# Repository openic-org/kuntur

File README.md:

# Kuntur

**Kuntur** (Quechua for *condor*) is an open neural-recording headstage
built around Intan RHD2164 amplifiers, a Lattice CrossLink-NX FPGA and an
STM32WB09 Bluetooth LE microcontroller, together with the firmware, FPGA
designs and desktop software that go with it.

> **Status: pre-release, research use only.** This repository is under
> active development ahead of a first public release. Interfaces, file
> formats and hardware revisions may still change. Not for clinical use.

Kuntur has two data paths:

- **Wireless:** the headstage streams over BLE (2M PHY) to a NUCLEO-WB09KE
  running the **BLE–USB bridge** firmware, which forwards packets over USB
  serial to **Tunki** (Quechua for the Andean cock-of-the-rock, Peru's
  national bird), the desktop app for live display and recording.
- **Wired:** the headstage sends its samples over an LVDS link to the
  **RHD adapter**, a CrossLink-NX FPGA design that appears to an RHD-protocol
  recording controller as two RHD2164 chips.

## Repository layout

```
hardware/      KiCad designs, fab packages, BOMs and pick-and-place files
  kuntur144-ecl/            headstage digital board: FPGA, BLE MCU, power
  kuntur144-nil/            headstage front-end board: recording and stimulation sheets
  kuntur144-omnetics/       Omnetics connector board
  kuntur144-prog/           programming board
  kuntur144-prog-adapter/   programming adapter
fpga/          Lattice Radiant projects
  headstage/                headstage FPGA (LIFCL-17)
  rhd-adapter/              RHD adapter (LIFCL-40)
  scripts/                  build and testbench helpers
firmware/
  headstage/                STM32WB09 headstage firmware (STM32CubeIDE project)
  ble-usb-bridge/           NUCLEO-WB09KE BLE central → USB serial bridge (Makefile)
software/
  tunki/                    PyQt6 desktop app: live display, recording, analysis
tools/                      analysis and validation tools (for now in software/tunki/)
```

## Building

**Tunki** (Python ≥ 3.11):

```bash
cd software/tunki
pip install -r requirements.txt
python main.py
```

**Firmware** needs the Arm GNU toolchain shipped with STM32CubeIDE and the
STM32Cube WB0 firmware packages (V1.4.0, and V1.4.1 for the bridge), found by
default under `~/STM32Cube/Repository`, where STM32CubeIDE installs them. For
another location, set `STM32CUBE_REPO` (bridge) or `STM32CUBE_FW_WB0` (headstage,
see `firmware/headstage/makefile.init`) on the `make` command line.

```bash
cd firmware/headstage/Debug && make all -j8     # → kuntur-mcu.elf / .hex
cd firmware/ble-usb-bridge && make -j8          # → build/ble_usb_bridge.bin
```

**FPGA** projects open in Lattice Radiant 2025.2 (`fpga/headstage/kuntur_fpga.rdf`,
`fpga/rhd-adapter/intan_rec_adapter.rdf`). Released bitstreams are tracked
next to each implementation (`impl_*/*.bit`).

## Licences

- `hardware/` and `fpga/`: **CERN Open Hardware Licence v2 – Permissive**
  (`LICENSES/CERN-OHL-P-2.0.txt`)
- everything else: **Apache License 2.0** (`LICENSES/Apache-2.0.txt`)

Third-party files (ST and Lattice generated code, the vendored bridge base in
`firmware/ble-usb-bridge/base/`) keep their own notices. See `LICENSE`.

Intan, RHD2164 and RHX are trademarks of Intan Technologies; this project is
not affiliated with or endorsed by Intan Technologies.

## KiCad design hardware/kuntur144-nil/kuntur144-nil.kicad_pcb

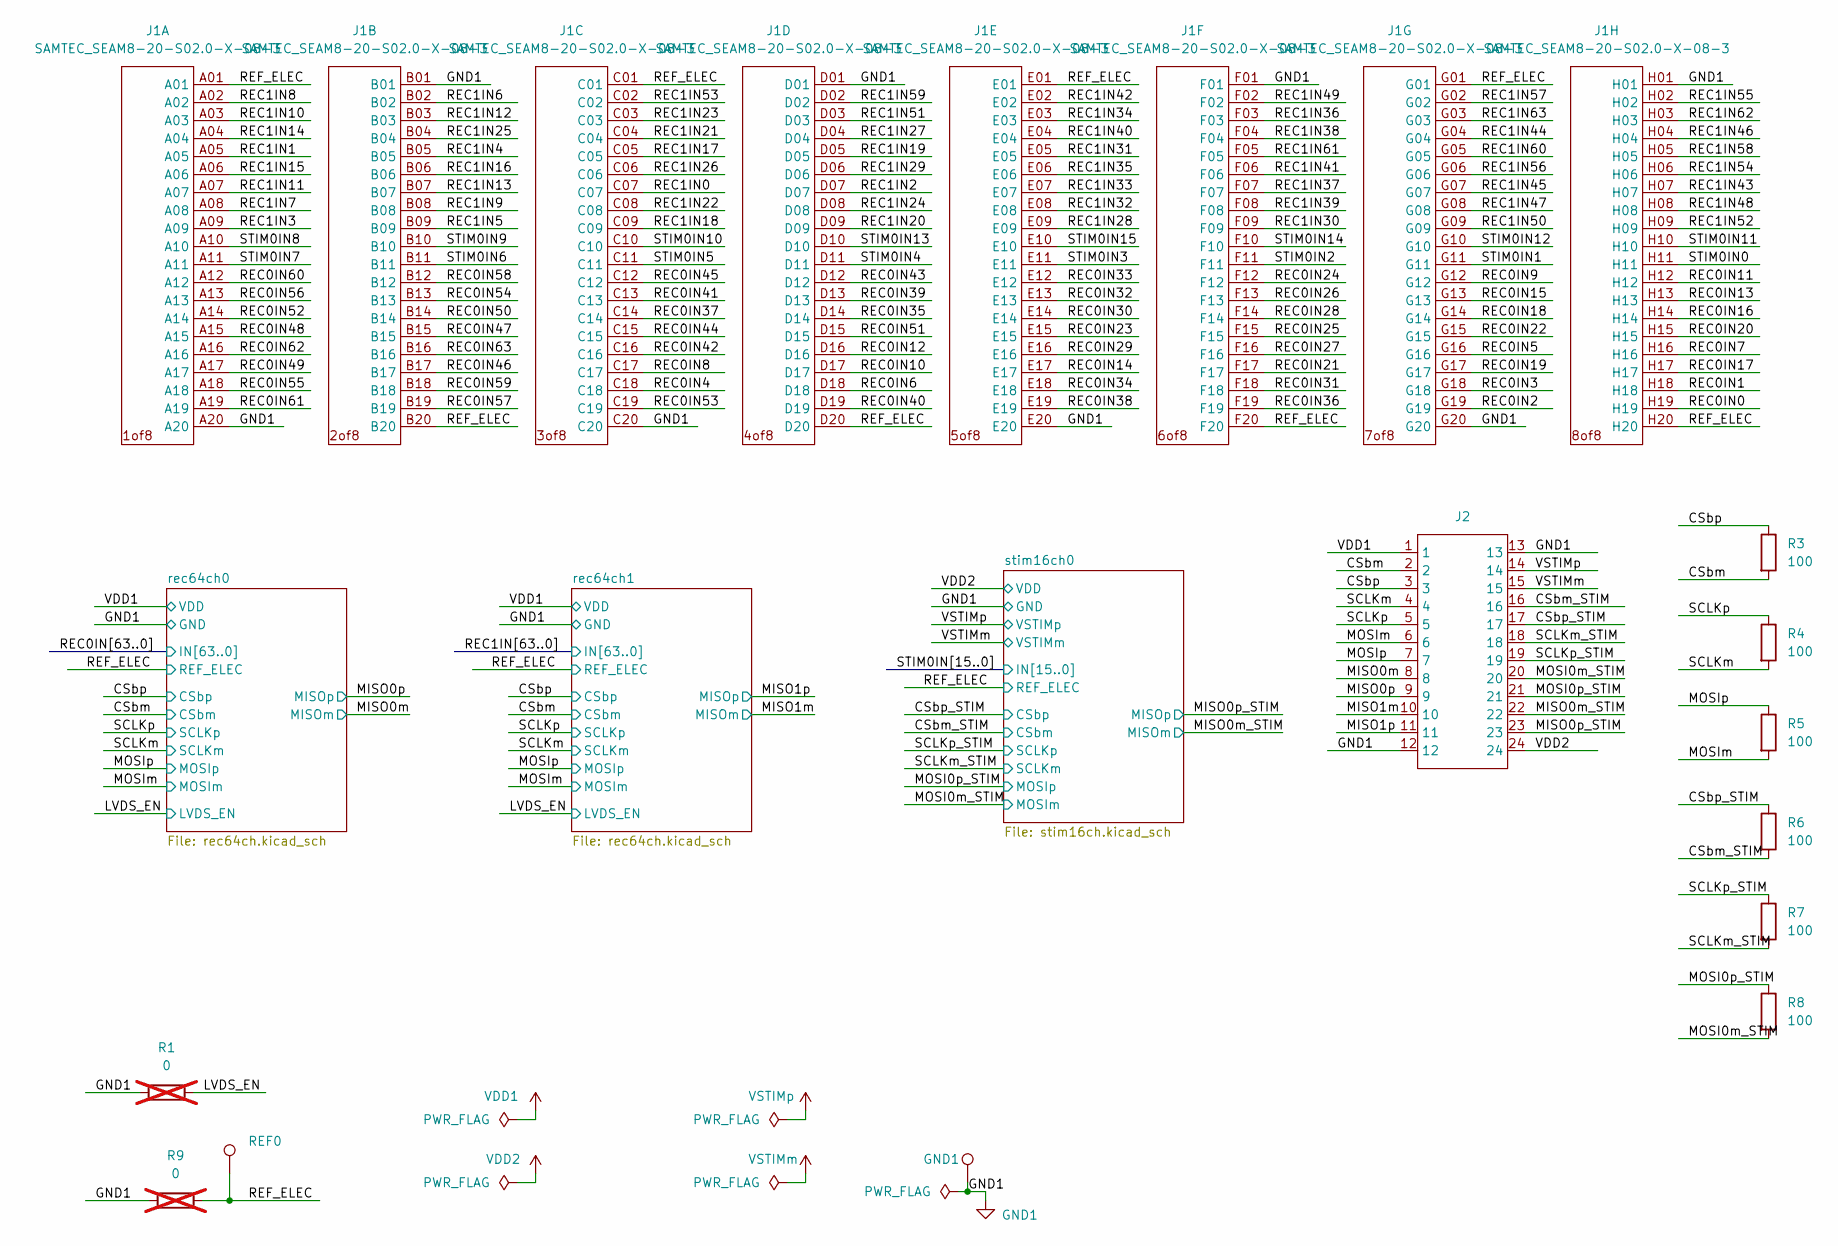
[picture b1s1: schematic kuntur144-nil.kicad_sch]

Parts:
GND1: GND1; TESTPOINT_SMALL
J1: SAMTEC_SEAM8-20-S02.0-X-08-3; MPN SEAM8-20-S02.0-S-08-3
J2: DF40C(2.0)-24DS-0.4V; MPN DF40C(2.0)-24DS-0.4V
R1, R9: 0; R_0201_0603Metric; MPN RC0201FR-070RL; not fitted
R3, R4, R5, R6, R7, R8: 100; R_0201_0603Metric; MPN RC0201FR-07100RL
REF0: REF0; TESTPOINT_SMALL

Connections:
/CSbm: J2.2, R3.2; also elsewhere on the board
/CSbm_STIM: J2.16, R6.2; also elsewhere on the board
/CSbp: J2.3, R3.1; also elsewhere on the board
/CSbp_STIM: J2.17, R6.1; also elsewhere on the board
/LVDS_EN: R1.2; also elsewhere on the board
/MISO0m: J2.8; also elsewhere on the board
/MISO0m_STIM: J2.22; also elsewhere on the board
/MISO0p: J2.9; also elsewhere on the board
/MISO0p_STIM: J2.23; also elsewhere on the board
/MISO1m: J2.10; also elsewhere on the board
/MISO1p: J2.11; also elsewhere on the board
/MOSI0m_STIM: J2.20, R8.2; also elsewhere on the board
/MOSI0p_STIM: J2.21, R8.1; also elsewhere on the board
/MOSIm: J2.6, R5.2; also elsewhere on the board
/MOSIp: J2.7, R5.1; also elsewhere on the board
/REC0IN0: J1.H19; also elsewhere on the board
/REC0IN1: J1.H18; also elsewhere on the board
/REC0IN2: J1.G19; also elsewhere on the board
/REC0IN3: J1.G18; also elsewhere on the board
/REC0IN4: J1.C18; also elsewhere on the board
/REC0IN5: J1.G16; also elsewhere on the board
/REC0IN6: J1.D18; also elsewhere on the board
/REC0IN7: J1.H16; also elsewhere on the board
/REC0IN8: J1.C17; also elsewhere on the board
/REC0IN9: J1.G12; also elsewhere on the board
/REC0IN10: J1.D17; also elsewhere on the board
/REC0IN11: J1.H12; also elsewhere on the board
/REC0IN12: J1.D16; also elsewhere on the board
/REC0IN13: J1.H13; also elsewhere on the board
/REC0IN14: J1.E17; also elsewhere on the board
/REC0IN15: J1.G13; also elsewhere on the board
/REC0IN16: J1.H14; also elsewhere on the board
/REC0IN17: J1.H17; also elsewhere on the board
/REC0IN18: J1.G14; also elsewhere on the board
/REC0IN19: J1.G17; also elsewhere on the board
/REC0IN20: J1.H15; also elsewhere on the board
/REC0IN21: J1.F17; also elsewhere on the board
/REC0IN22: J1.G15; also elsewhere on the board
/REC0IN23: J1.E15; also elsewhere on the board
/REC0IN24: J1.F12; also elsewhere on the board
/REC0IN25: J1.F15; also elsewhere on the board
/REC0IN26: J1.F13; also elsewhere on the board
/REC0IN27: J1.F16; also elsewhere on the board
/REC0IN28: J1.F14; also elsewhere on the board
/REC0IN29: J1.E16; also elsewhere on the board
/REC0IN30: J1.E14; also elsewhere on the board
/REC0IN31: J1.F18; also elsewhere on the board
/REC0IN32: J1.E13; also elsewhere on the board
/REC0IN33: J1.E12; also elsewhere on the board
/REC0IN34: J1.E18; also elsewhere on the board
/REC0IN35: J1.D14; also elsewhere on the board
/REC0IN36: J1.F19; also elsewhere on the board
/REC0IN37: J1.C14; also elsewhere on the board
/REC0IN38: J1.E19; also elsewhere on the board
/REC0IN39: J1.D13; also elsewhere on the board
/REC0IN40: J1.D19; also elsewhere on the board
/REC0IN41: J1.C13; also elsewhere on the board
/REC0IN42: J1.C16; also elsewhere on the board
/REC0IN43: J1.D12; also elsewhere on the board
/REC0IN44: J1.C15; also elsewhere on the board
/REC0IN45: J1.C12; also elsewhere on the board
/REC0IN46: J1.B17; also elsewhere on the board
/REC0IN47: J1.B15; also elsewhere on the board
/REC0IN48: J1.A15; also elsewhere on the board
/REC0IN49: J1.A17; also elsewhere on the board
/REC0IN50: J1.B14; also elsewhere on the board
/REC0IN51: J1.D15; also elsewhere on the board
/REC0IN52: J1.A14; also elsewhere on the board
/REC0IN53: J1.C19; also elsewhere on the board
/REC0IN54: J1.B13; also elsewhere on the board
/REC0IN55: J1.A18; also elsewhere on the board
/REC0IN56: J1.A13; also elsewhere on the board
/REC0IN57: J1.B19; also elsewhere on the board
/REC0IN58: J1.B12; also elsewhere on the board
/REC0IN59: J1.B18; also elsewhere on the board
/REC0IN60: J1.A12; also elsewhere on the board
/REC0IN61: J1.A19; also elsewhere on the board
/REC0IN62: J1.A16; also elsewhere on the board
/REC0IN63: J1.B16; also elsewhere on the board
/REC1IN0: J1.C07; also elsewhere on the board
/REC1IN1: J1.A05; also elsewhere on the board
/REC1IN2: J1.D07; also elsewhere on the board
/REC1IN3: J1.A09; also elsewhere on the board
/REC1IN4: J1.B05; also elsewhere on the board
/REC1IN5: J1.B09; also elsewhere on the board
/REC1IN6: J1.B02; also elsewhere on the board
/REC1IN7: J1.A08; also elsewhere on the board
/REC1IN8: J1.A02; also elsewhere on the board
/REC1IN9: J1.B08; also elsewhere on the board
/REC1IN10: J1.A03; also elsewhere on the board
/REC1IN11: J1.A07; also elsewhere on the board
/REC1IN12: J1.B03; also elsewhere on the board
/REC1IN13: J1.B07; also elsewhere on the board
/REC1IN14: J1.A04; also elsewhere on the board
/REC1IN15: J1.A06; also elsewhere on the board
/REC1IN16: J1.B06; also elsewhere on the board
/REC1IN17: J1.C05; also elsewhere on the board
/REC1IN18: J1.C09; also elsewhere on the board
/REC1IN19: J1.D05; also elsewhere on the board
/REC1IN20: J1.D09; also elsewhere on the board
/REC1IN21: J1.C04; also elsewhere on the board
/REC1IN22: J1.C08; also elsewhere on the board
/REC1IN23: J1.C03; also elsewhere on the board
/REC1IN24: J1.D08; also elsewhere on the board
/REC1IN25: J1.B04; also elsewhere on the board
/REC1IN26: J1.C06; also elsewhere on the board
/REC1IN27: J1.D04; also elsewhere on the board
/REC1IN28: J1.E09; also elsewhere on the board
/REC1IN29: J1.D06; also elsewhere on the board
/REC1IN30: J1.F09; also elsewhere on the board
/REC1IN31: J1.E05; also elsewhere on the board
/REC1IN32: J1.E08; also elsewhere on the board
/REC1IN33: J1.E07; also elsewhere on the board
/REC1IN34: J1.E03; also elsewhere on the board
/REC1IN35: J1.E06; also elsewhere on the board
/REC1IN36: J1.F03; also elsewhere on the board
/REC1IN37: J1.F07; also elsewhere on the board
/REC1IN38: J1.F04; also elsewhere on the board
/REC1IN39: J1.F08; also elsewhere on the board
/REC1IN40: J1.E04; also elsewhere on the board
/REC1IN41: J1.F06; also elsewhere on the board
/REC1IN42: J1.E02; also elsewhere on the board
/REC1IN43: J1.H07; also elsewhere on the board
/REC1IN44: J1.G04; also elsewhere on the board
/REC1IN45: J1.G07; also elsewhere on the board
/REC1IN46: J1.H04; also elsewhere on the board
/REC1IN47: J1.G08; also elsewhere on the board
/REC1IN48: J1.H08; also elsewhere on the board
/REC1IN49: J1.F02; also elsewhere on the board
/REC1IN50: J1.G09; also elsewhere on the board
/REC1IN51: J1.D03; also elsewhere on the board
/REC1IN52: J1.H09; also elsewhere on the board
/REC1IN53: J1.C02; also elsewhere on the board
/REC1IN54: J1.H06; also elsewhere on the board
/REC1IN55: J1.H02; also elsewhere on the board
/REC1IN56: J1.G06; also elsewhere on the board
/REC1IN57: J1.G02; also elsewhere on the board
/REC1IN58: J1.H05; also elsewhere on the board
/REC1IN59: J1.D02; also elsewhere on the board
/REC1IN60: J1.G05; also elsewhere on the board
/REC1IN61: J1.F05; also elsewhere on the board
/REC1IN62: J1.H03; also elsewhere on the board
/REC1IN63: J1.G03; also elsewhere on the board
/REF_ELEC: J1.A01, J1.B20, J1.C01, J1.D20, J1.E01, J1.F20, J1.G01, J1.H20, R9.2, REF0.1; also elsewhere on the board
/SCLKm: J2.4, R4.2; also elsewhere on the board
/SCLKm_STIM: J2.18, R7.2; also elsewhere on the board
/SCLKp: J2.5, R4.1; also elsewhere on the board
/SCLKp_STIM: J2.19, R7.1; also elsewhere on the board
/STIM0IN0: J1.H11; also elsewhere on the board
/STIM0IN1: J1.G11; also elsewhere on the board
/STIM0IN2: J1.F11; also elsewhere on the board
/STIM0IN3: J1.E11; also elsewhere on the board
/STIM0IN4: J1.D11; also elsewhere on the board
/STIM0IN5: J1.C11; also elsewhere on the board
/STIM0IN6: J1.B11; also elsewhere on the board
/STIM0IN7: J1.A11; also elsewhere on the board
/STIM0IN8: J1.A10; also elsewhere on the board
/STIM0IN9: J1.B10; also elsewhere on the board
/STIM0IN10: J1.C10; also elsewhere on the board
/STIM0IN11: J1.H10; also elsewhere on the board
/STIM0IN12: J1.G10; also elsewhere on the board
/STIM0IN13: J1.D10; also elsewhere on the board
/STIM0IN14: J1.F10; also elsewhere on the board
/STIM0IN15: J1.E10; also elsewhere on the board
GND1: GND1.1, J1.A20, J1.B01, J1.C20, J1.D01, J1.E20, J1.F01, J1.G20, J1.H01, J2.12, J2.13, R1.1, R9.1; also elsewhere on the board
VDD1: J2.1; also elsewhere on the board
VDD2: J2.24; also elsewhere on the board
VSTIMm: J2.15; also elsewhere on the board
VSTIMp: J2.14; also elsewhere on the board

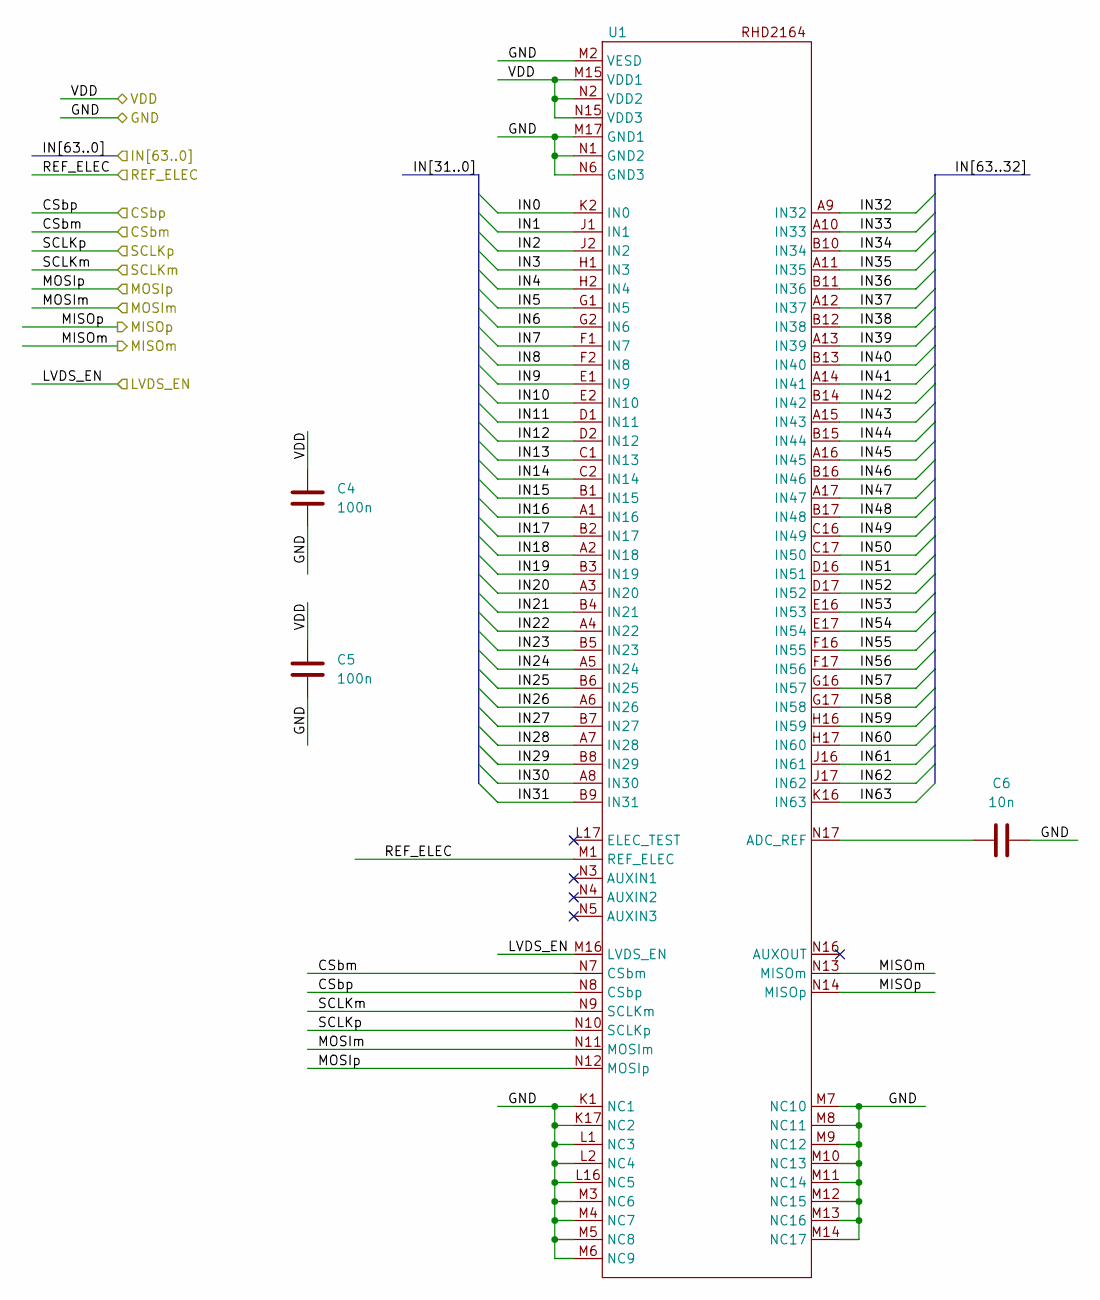
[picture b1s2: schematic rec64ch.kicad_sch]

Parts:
C4, C5: 100n; C_0201_0603Metric; MPN C0603X5R1C104K030BC
C6: 10n; C_0201_0603Metric; MPN GRM033R61C103KA12D
U1: 104-Pin BGA - 9mmx7mm; MPN RHD2164

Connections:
/CSbm: U1.N7 (CSbm); also elsewhere on the board
/CSbp: U1.N8 (CSbp); also elsewhere on the board
/LVDS_EN: U1.M16 (LVDS_EN); also elsewhere on the board
/MISO1m: U1.N13 (MISOm); also elsewhere on the board
/MISO1p: U1.N14 (MISOp); also elsewhere on the board
/MOSIm: U1.N11 (MOSIm); also elsewhere on the board
/MOSIp: U1.N12 (MOSIp); also elsewhere on the board
/REC1IN0: U1.K2 (IN0); also elsewhere on the board
/REC1IN1: U1.J1 (IN1); also elsewhere on the board
/REC1IN2: U1.J2 (IN2); also elsewhere on the board
/REC1IN3: U1.H1 (IN3); also elsewhere on the board
/REC1IN4: U1.H2 (IN4); also elsewhere on the board
/REC1IN5: U1.G1 (IN5); also elsewhere on the board
/REC1IN6: U1.G2 (IN6); also elsewhere on the board
/REC1IN7: U1.F1 (IN7); also elsewhere on the board
/REC1IN8: U1.F2 (IN8); also elsewhere on the board
/REC1IN9: U1.E1 (IN9); also elsewhere on the board
/REC1IN10: U1.E2 (IN10); also elsewhere on the board
/REC1IN11: U1.D1 (IN11); also elsewhere on the board
/REC1IN12: U1.D2 (IN12); also elsewhere on the board
/REC1IN13: U1.C1 (IN13); also elsewhere on the board
/REC1IN14: U1.C2 (IN14); also elsewhere on the board
/REC1IN15: U1.B1 (IN15); also elsewhere on the board
/REC1IN16: U1.A1 (IN16); also elsewhere on the board
/REC1IN17: U1.B2 (IN17); also elsewhere on the board
/REC1IN18: U1.A2 (IN18); also elsewhere on the board
/REC1IN19: U1.B3 (IN19); also elsewhere on the board
/REC1IN20: U1.A3 (IN20); also elsewhere on the board
/REC1IN21: U1.B4 (IN21); also elsewhere on the board
/REC1IN22: U1.A4 (IN22); also elsewhere on the board
/REC1IN23: U1.B5 (IN23); also elsewhere on the board
/REC1IN24: U1.A5 (IN24); also elsewhere on the board
/REC1IN25: U1.B6 (IN25); also elsewhere on the board
/REC1IN26: U1.A6 (IN26); also elsewhere on the board
/REC1IN27: U1.B7 (IN27); also elsewhere on the board
/REC1IN28: U1.A7 (IN28); also elsewhere on the board
/REC1IN29: U1.B8 (IN29); also elsewhere on the board
/REC1IN30: U1.A8 (IN30); also elsewhere on the board
/REC1IN31: U1.B9 (IN31); also elsewhere on the board
/REC1IN32: U1.A9 (IN32); also elsewhere on the board
/REC1IN33: U1.A10 (IN33); also elsewhere on the board
/REC1IN34: U1.B10 (IN34); also elsewhere on the board
/REC1IN35: U1.A11 (IN35); also elsewhere on the board
/REC1IN36: U1.B11 (IN36); also elsewhere on the board
/REC1IN37: U1.A12 (IN37); also elsewhere on the board
/REC1IN38: U1.B12 (IN38); also elsewhere on the board
/REC1IN39: U1.A13 (IN39); also elsewhere on the board
/REC1IN40: U1.B13 (IN40); also elsewhere on the board
/REC1IN41: U1.A14 (IN41); also elsewhere on the board
/REC1IN42: U1.B14 (IN42); also elsewhere on the board
/REC1IN43: U1.A15 (IN43); also elsewhere on the board
/REC1IN44: U1.B15 (IN44); also elsewhere on the board
/REC1IN45: U1.A16 (IN45); also elsewhere on the board
/REC1IN46: U1.B16 (IN46); also elsewhere on the board
/REC1IN47: U1.A17 (IN47); also elsewhere on the board
/REC1IN48: U1.B17 (IN48); also elsewhere on the board
/REC1IN49: U1.C16 (IN49); also elsewhere on the board
/REC1IN50: U1.C17 (IN50); also elsewhere on the board
/REC1IN51: U1.D16 (IN51); also elsewhere on the board
/REC1IN52: U1.D17 (IN52); also elsewhere on the board
/REC1IN53: U1.E16 (IN53); also elsewhere on the board
/REC1IN54: U1.E17 (IN54); also elsewhere on the board
/REC1IN55: U1.F16 (IN55); also elsewhere on the board
/REC1IN56: U1.F17 (IN56); also elsewhere on the board
/REC1IN57: U1.G16 (IN57); also elsewhere on the board
/REC1IN58: U1.G17 (IN58); also elsewhere on the board
/REC1IN59: U1.H16 (IN59); also elsewhere on the board
/REC1IN60: U1.H17 (IN60); also elsewhere on the board
/REC1IN61: U1.J16 (IN61); also elsewhere on the board
/REC1IN62: U1.J17 (IN62); also elsewhere on the board
/REC1IN63: U1.K16 (IN63); also elsewhere on the board
/REF_ELEC: U1.M1 (REF_ELEC); also elsewhere on the board
/SCLKm: U1.N9 (SCLKm); also elsewhere on the board
/SCLKp: U1.N10 (SCLKp); also elsewhere on the board
GND1: C4.2, C5.2, C6.2, U1.K1 (NC1), U1.K17 (NC2), U1.L1 (NC3), U1.L2 (NC4), U1.L16 (NC5), U1.M2 (VESD), U1.M3 (NC6), U1.M4 (NC7), U1.M5 (NC8), U1.M6 (NC9), U1.M7 (NC10), U1.M8 (NC11), U1.M9 (NC12), U1.M10 (NC13), U1.M11 (NC14), U1.M12 (NC15), U1.M13 (NC16), U1.M14 (NC17), U1.M17 (GND1), U1.N1 (GND2), U1.N6 (GND3); also elsewhere on the board
unnamed: C6.1, U1.N17 (ADC_REF)
VDD1: C4.1, C5.1, U1.M15 (VDD1), U1.N2 (VDD2), U1.N15 (VDD3); also elsewhere on the board

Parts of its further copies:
C1, C2: 100n; C_0201_0603Metric; MPN C0603X5R1C104K030BC
C3: 10n; C_0201_0603Metric; MPN GRM033R61C103KA12D
U0: 104-Pin BGA - 9mmx7mm; MPN RHD2164

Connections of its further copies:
/CSbm: U0.N7 (CSbm); also elsewhere on the board
/CSbp: U0.N8 (CSbp); also elsewhere on the board
/LVDS_EN: U0.M16 (LVDS_EN); also elsewhere on the board
/MISO0m: U0.N13 (MISOm); also elsewhere on the board
/MISO0p: U0.N14 (MISOp); also elsewhere on the board
/MOSIm: U0.N11 (MOSIm); also elsewhere on the board
/MOSIp: U0.N12 (MOSIp); also elsewhere on the board
/REC0IN0: U0.K2 (IN0); also elsewhere on the board
/REC0IN1: U0.J1 (IN1); also elsewhere on the board
/REC0IN2: U0.J2 (IN2); also elsewhere on the board
/REC0IN3: U0.H1 (IN3); also elsewhere on the board
/REC0IN4: U0.H2 (IN4); also elsewhere on the board
/REC0IN5: U0.G1 (IN5); also elsewhere on the board
/REC0IN6: U0.G2 (IN6); also elsewhere on the board
/REC0IN7: U0.F1 (IN7); also elsewhere on the board
/REC0IN8: U0.F2 (IN8); also elsewhere on the board
/REC0IN9: U0.E1 (IN9); also elsewhere on the board
/REC0IN10: U0.E2 (IN10); also elsewhere on the board
/REC0IN11: U0.D1 (IN11); also elsewhere on the board
/REC0IN12: U0.D2 (IN12); also elsewhere on the board
/REC0IN13: U0.C1 (IN13); also elsewhere on the board
/REC0IN14: U0.C2 (IN14); also elsewhere on the board
/REC0IN15: U0.B1 (IN15); also elsewhere on the board
/REC0IN16: U0.A1 (IN16); also elsewhere on the board
/REC0IN17: U0.B2 (IN17); also elsewhere on the board
/REC0IN18: U0.A2 (IN18); also elsewhere on the board
/REC0IN19: U0.B3 (IN19); also elsewhere on the board
/REC0IN20: U0.A3 (IN20); also elsewhere on the board
/REC0IN21: U0.B4 (IN21); also elsewhere on the board
/REC0IN22: U0.A4 (IN22); also elsewhere on the board
/REC0IN23: U0.B5 (IN23); also elsewhere on the board
/REC0IN24: U0.A5 (IN24); also elsewhere on the board
/REC0IN25: U0.B6 (IN25); also elsewhere on the board
/REC0IN26: U0.A6 (IN26); also elsewhere on the board
/REC0IN27: U0.B7 (IN27); also elsewhere on the board
/REC0IN28: U0.A7 (IN28); also elsewhere on the board
/REC0IN29: U0.B8 (IN29); also elsewhere on the board
/REC0IN30: U0.A8 (IN30); also elsewhere on the board
/REC0IN31: U0.B9 (IN31); also elsewhere on the board
/REC0IN32: U0.A9 (IN32); also elsewhere on the board
/REC0IN33: U0.A10 (IN33); also elsewhere on the board
/REC0IN34: U0.B10 (IN34); also elsewhere on the board
/REC0IN35: U0.A11 (IN35); also elsewhere on the board
/REC0IN36: U0.B11 (IN36); also elsewhere on the board
/REC0IN37: U0.A12 (IN37); also elsewhere on the board
/REC0IN38: U0.B12 (IN38); also elsewhere on the board
/REC0IN39: U0.A13 (IN39); also elsewhere on the board
/REC0IN40: U0.B13 (IN40); also elsewhere on the board
/REC0IN41: U0.A14 (IN41); also elsewhere on the board
/REC0IN42: U0.B14 (IN42); also elsewhere on the board
/REC0IN43: U0.A15 (IN43); also elsewhere on the board
/REC0IN44: U0.B15 (IN44); also elsewhere on the board
/REC0IN45: U0.A16 (IN45); also elsewhere on the board
/REC0IN46: U0.B16 (IN46); also elsewhere on the board
/REC0IN47: U0.A17 (IN47); also elsewhere on the board
/REC0IN48: U0.B17 (IN48); also elsewhere on the board
/REC0IN49: U0.C16 (IN49); also elsewhere on the board
/REC0IN50: U0.C17 (IN50); also elsewhere on the board
/REC0IN51: U0.D16 (IN51); also elsewhere on the board
/REC0IN52: U0.D17 (IN52); also elsewhere on the board
/REC0IN53: U0.E16 (IN53); also elsewhere on the board
/REC0IN54: U0.E17 (IN54); also elsewhere on the board
/REC0IN55: U0.F16 (IN55); also elsewhere on the board
/REC0IN56: U0.F17 (IN56); also elsewhere on the board
/REC0IN57: U0.G16 (IN57); also elsewhere on the board
/REC0IN58: U0.G17 (IN58); also elsewhere on the board
/REC0IN59: U0.H16 (IN59); also elsewhere on the board
/REC0IN60: U0.H17 (IN60); also elsewhere on the board
/REC0IN61: U0.J16 (IN61); also elsewhere on the board
/REC0IN62: U0.J17 (IN62); also elsewhere on the board
/REC0IN63: U0.K16 (IN63); also elsewhere on the board
/REF_ELEC: U0.M1 (REF_ELEC); also elsewhere on the board
/SCLKm: U0.N9 (SCLKm); also elsewhere on the board
/SCLKp: U0.N10 (SCLKp); also elsewhere on the board
GND1: C1.2, C2.2, C3.2, U0.K1 (NC1), U0.K17 (NC2), U0.L1 (NC3), U0.L2 (NC4), U0.L16 (NC5), U0.M2 (VESD), U0.M3 (NC6), U0.M4 (NC7), U0.M5 (NC8), U0.M6 (NC9), U0.M7 (NC10), U0.M8 (NC11), U0.M9 (NC12), U0.M10 (NC13), U0.M11 (NC14), U0.M12 (NC15), U0.M13 (NC16), U0.M14 (NC17), U0.M17 (GND1), U0.N1 (GND2), U0.N6 (GND3); also elsewhere on the board
unnamed: C3.1, U0.N17 (ADC_REF)
VDD1: C1.1, C2.1, U0.M15 (VDD1), U0.N2 (VDD2), U0.N15 (VDD3); also elsewhere on the board

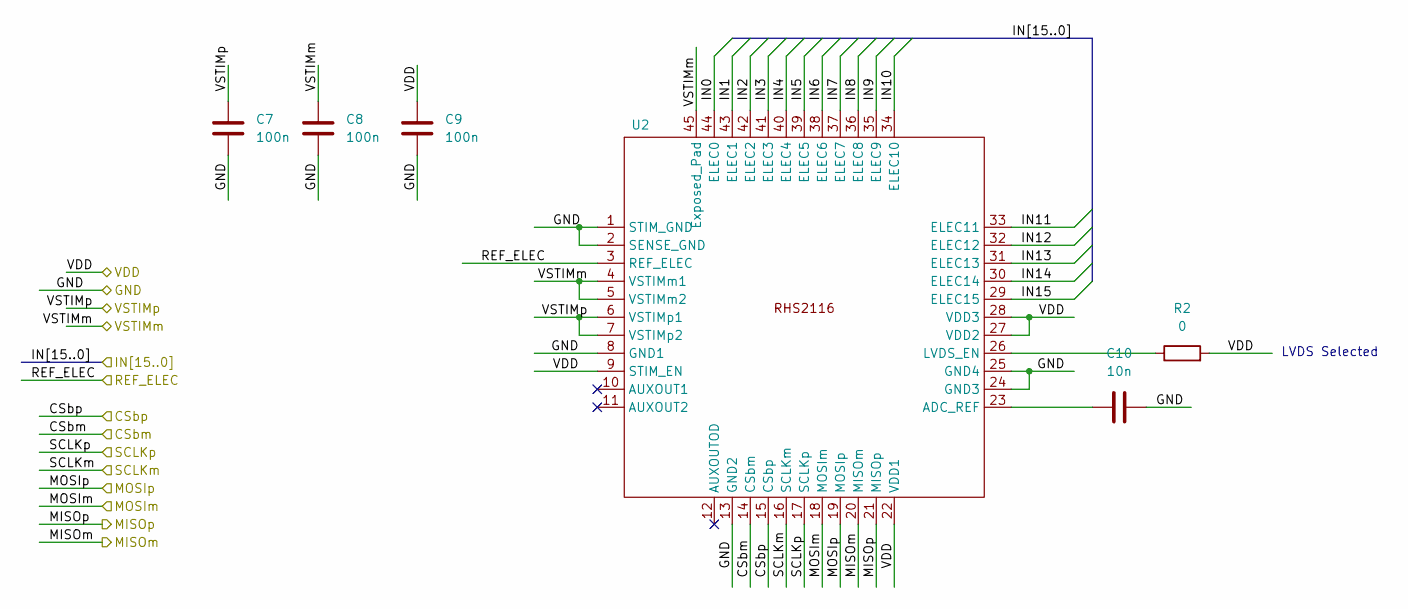
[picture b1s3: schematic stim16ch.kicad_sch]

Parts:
C7, C8, C9: 100n; C_0201_0603Metric; MPN C0603X5R1C104K030BC
C10: 10n; C_0201_0603Metric; MPN GRM033R61C103KA12D
R2: 0; R_0201_0603Metric; MPN RC0201FR-070RL
U2: QFN-44-1EP_7x7mm_P0.5mm_EP5.4x5.4mm; MPN RHS2116

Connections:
/CSbm_STIM: U2.14 (CSbm); also elsewhere on the board
/CSbp_STIM: U2.15 (CSbp); also elsewhere on the board
/MISO0m_STIM: U2.20 (MISOm); also elsewhere on the board
/MISO0p_STIM: U2.21 (MISOp); also elsewhere on the board
/MOSI0m_STIM: U2.18 (MOSIm); also elsewhere on the board
/MOSI0p_STIM: U2.19 (MOSIp); also elsewhere on the board
/REF_ELEC: U2.3 (REF_ELEC); also elsewhere on the board
/SCLKm_STIM: U2.16 (SCLKm); also elsewhere on the board
/SCLKp_STIM: U2.17 (SCLKp); also elsewhere on the board
/STIM0IN0: U2.44 (ELEC0); also elsewhere on the board
/STIM0IN1: U2.43 (ELEC1); also elsewhere on the board
/STIM0IN2: U2.42 (ELEC2); also elsewhere on the board
/STIM0IN3: U2.41 (ELEC3); also elsewhere on the board
/STIM0IN4: U2.40 (ELEC4); also elsewhere on the board
/STIM0IN5: U2.39 (ELEC5); also elsewhere on the board
/STIM0IN6: U2.38 (ELEC6); also elsewhere on the board
/STIM0IN7: U2.37 (ELEC7); also elsewhere on the board
/STIM0IN8: U2.36 (ELEC8); also elsewhere on the board
/STIM0IN9: U2.35 (ELEC9); also elsewhere on the board
/STIM0IN10: U2.34 (ELEC10); also elsewhere on the board
/STIM0IN11: U2.33 (ELEC11); also elsewhere on the board
/STIM0IN12: U2.32 (ELEC12); also elsewhere on the board
/STIM0IN13: U2.31 (ELEC13); also elsewhere on the board
/STIM0IN14: U2.30 (ELEC14); also elsewhere on the board
/STIM0IN15: U2.29 (ELEC15); also elsewhere on the board
GND1: C7.2, C8.2, C9.2, C10.2, U2.1 (STIM_GND), U2.2 (SENSE_GND), U2.8 (GND1), U2.13 (GND2), U2.24 (GND3), U2.25 (GND4); also elsewhere on the board
unnamed: C10.1, U2.23 (ADC_REF)
unnamed: R2.1, U2.26 (LVDS_EN)
VDD2: C9.1, R2.2, U2.9 (STIM_EN), U2.22 (VDD1), U2.27 (VDD2), U2.28 (VDD3); also elsewhere on the board
VSTIMm: C8.1, U2.4 (VSTIMm1), U2.5 (VSTIMm2), U2.45 (Exposed_Pad); also elsewhere on the board
VSTIMp: C7.1, U2.6 (VSTIMp1), U2.7 (VSTIMp2); also elsewhere on the board

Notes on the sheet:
LVDS Selected

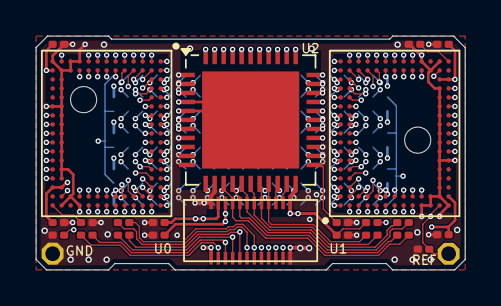
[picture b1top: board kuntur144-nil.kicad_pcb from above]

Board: 8 copper layers, 23.8 x 13.0 mm, 26 parts (1 on the bottom side), 173 nets.

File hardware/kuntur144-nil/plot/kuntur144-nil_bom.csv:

"Reference","Value","Qty","DNP","MPN","Manufacturer"
"C1,C2,C4,C5,C7,C8,C9","100n","7","","C0603X5R1C104K030BC","TDK"
"C3,C6,C10","10n","3","","GRM033R61C103KA12D","Murata Electronics"
"GND1","GND1","1","","~",""
"J1","~","1","","SEAM8-20-S02.0-S-08-3","Samtec"
"J2","~","1","","DF40C(2.0)-24DS-0.4V","Hirose"
"R1,R9","0","2","DNP","RC0201FR-070RL","Yageo"
"R2","0","1","","RC0201FR-070RL","Yageo"
"R3,R4,R5,R6,R7,R8","100","6","","RC0201FR-07100RL","Yageo"
"REF0","REF0","1","","~",""
"U0,U1","~","2","","RHD2164","Intan Technologies"
"U2","~","1","","RHS2116","Intan Technologies"

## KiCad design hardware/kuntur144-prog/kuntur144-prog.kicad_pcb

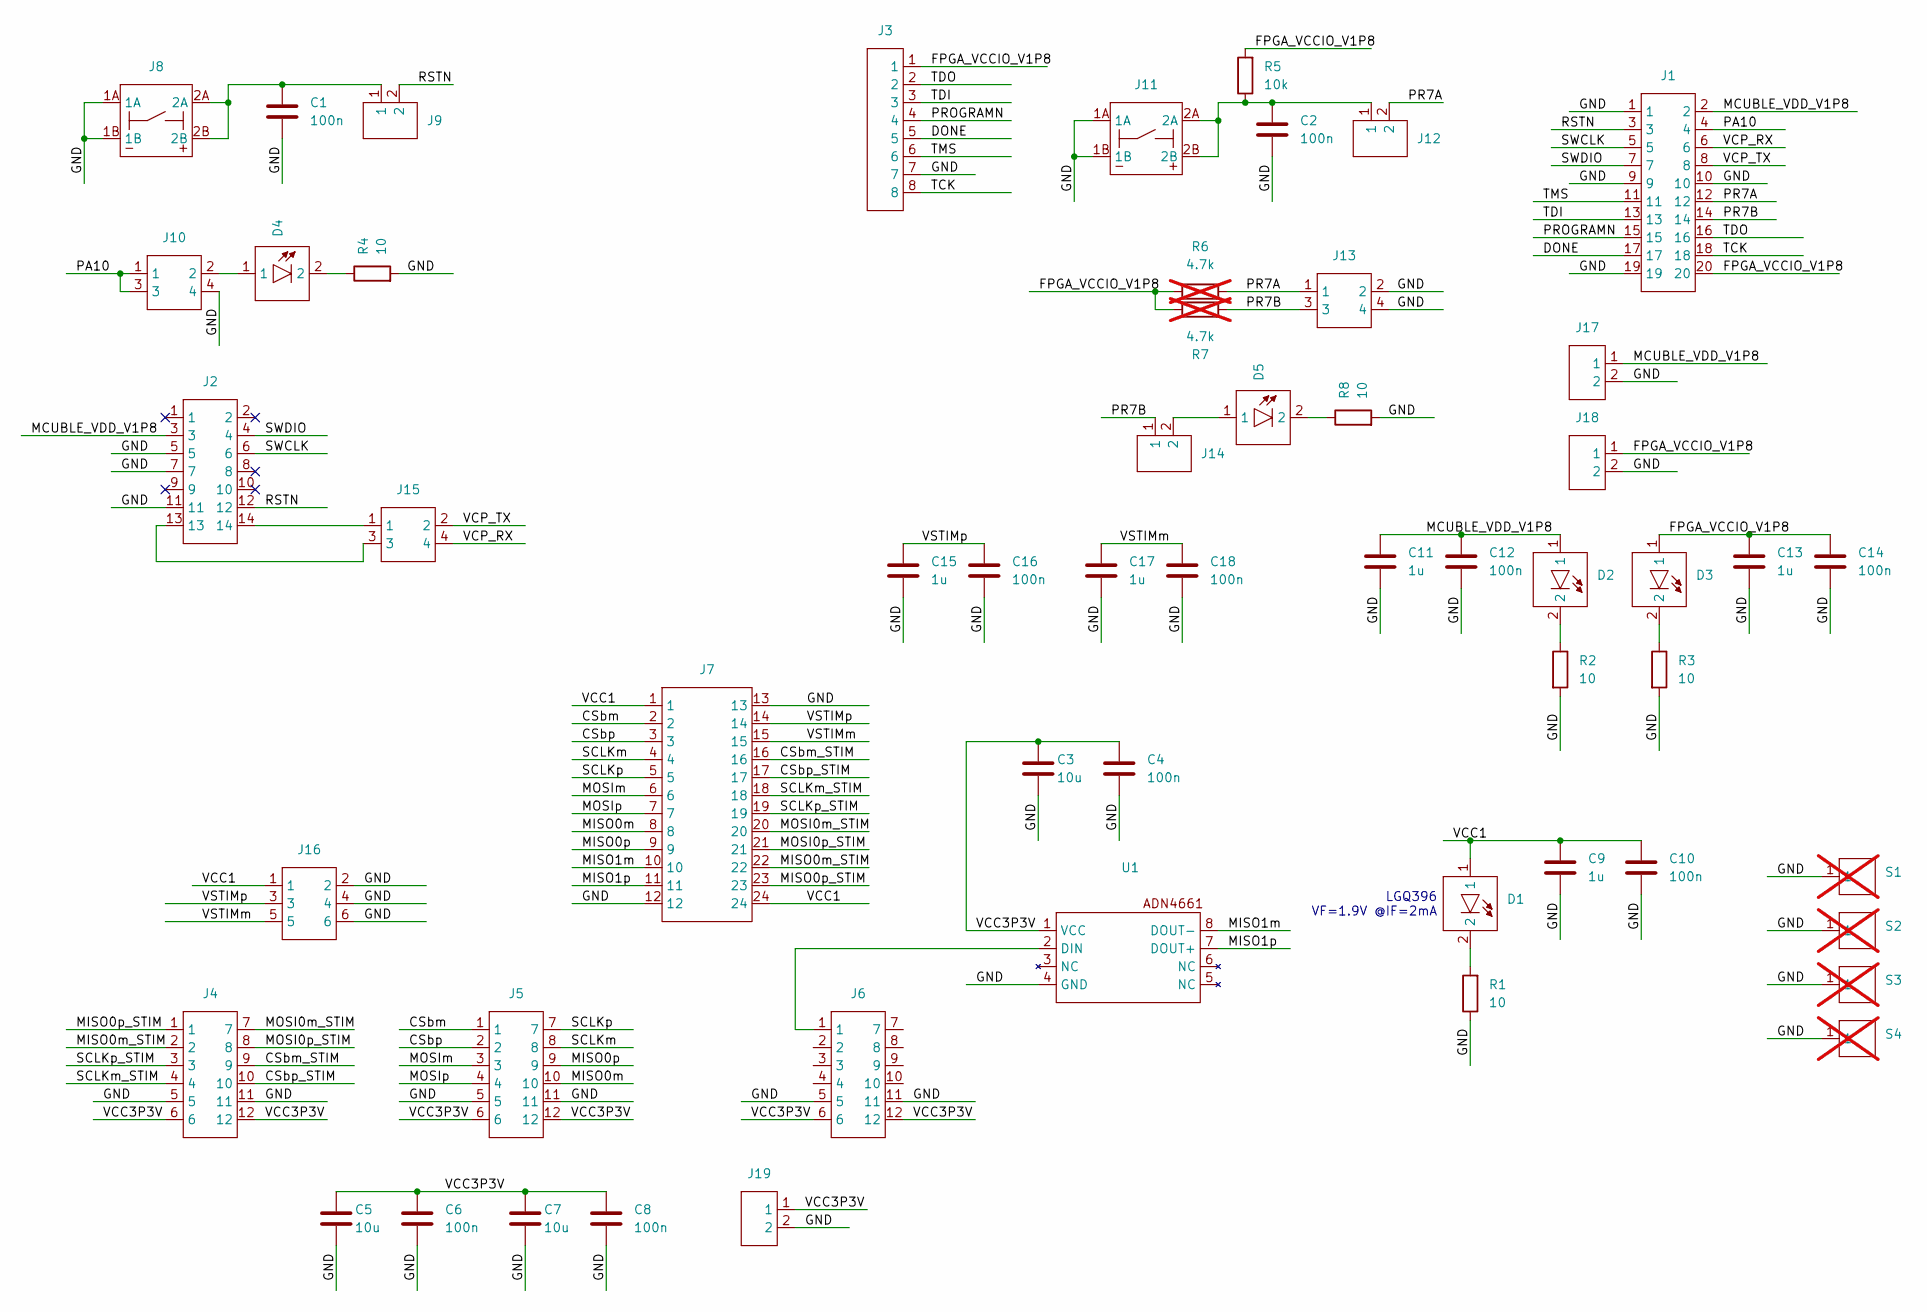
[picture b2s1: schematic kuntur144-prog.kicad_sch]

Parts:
C1, C2, C4, C6, C8, C10, C12, C14, C16, C18: 100n; C_0402_1005Metric; MPN GRM155R61C104KA88D
C3, C5, C7: 10u; SMD_C_0603_10UF_6.3V_GRM185R60J106ME15; MPN GRM185R60J106ME15J
C9, C11, C13, C15, C17: 1u; C_0402_1005Metric; MPN GRM155R61C105KA12J
D1: OSRAM-LED-0603; MPN LGQ396
D2, D3, D4, D5: ROHM-LED-0603; MPN CSL1901UW1
J1: SMD-20_2x10_P0.05in; MPN FTSH-110-01-L-DV-K
J2: SMD-14_2x7_P0.05in; MPN FTSH-107-01-L-DV-K
J3: HEADER-8-1x8-P0.1in; MPN PH1-08-UA
J4, J5, J6: PMOD-MALE-RA-12-2x6-P0.1in; MPN PH2RA-12-UA
J7: DF40C(2.0)-24DS-0.4V; MPN DF40C(2.0)-24DS-0.4V(51)
J8, J11: BOURNES-PUSHBUTTON-7914G-1-000; MPN 7914G-1-000
J9, J12, J14, J17, J18, J19: HEADER-2-1x2-P0.1in; MPN PH1-02-UA
J10, J13, J15: HEADER-4-2x2-P0.1in; MPN M20-9760246
J16: HEADER-6-2x3-P0.1in; MPN M20-9980346
R1, R2, R3, R4, R8: 10; R_0402_1005Metric; MPN RC0402FR-7W10RL
R5: 10k; R_0402_1005Metric; MPN RC0402FR-7W10KL
R6, R7: 4.7k; R_0402_1005Metric; MPN RC0402FR-7W4K7L; not fitted
S1, S2, S3, S4: MOUNTING_HOLE-PAD-0.1IN; MPN None; not fitted
U1: SOIC-8_3.9x4.9mm_P1.27mm; MPN ADN4661BRZ-REEL7

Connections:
/CSbm: J5.1, J7.2
/CSbm_STIM: J4.9, J7.16
/CSbp: J5.2, J7.3
/CSbp_STIM: J4.10, J7.17
/DONE: J1.17, J3.5
/FPGA_VCCIO_V1P8: C13.1, C14.1, D3.1, J1.20, J3.1, J18.1, R5.2, R6.2, R7.2
/GND: C1.2, C2.2, C3.2, C4.2, C5.2, C6.2, C7.2, C8.2, C9.2, C10.2, C11.2, C12.2, C13.2, C14.2, C15.2, C16.2, C17.2, C18.2, J1.1, J1.9, J1.10, J1.19, J2.5, J2.7, J2.11, J3.7, J4.5, J4.11, J5.5, J5.11, J6.5, J6.11, J7.12, J7.13, J8.1A, J8.1B, J10.4, J11.1A, J11.1B, J13.2, J13.4, J16.2, J16.4, J16.6, J17.2, J18.2, J19.2, R1.1, R2.2, R3.2, R4.2, R8.2, S1.1, S2.1, S3.1, S4.1, U1.4 (GND)
/MCUBLE_VDD_V1P8: C11.1, C12.1, D2.1, J1.2, J2.3, J17.1
/MISO0m: J5.10, J7.8
/MISO0m_STIM: J4.2, J7.22
/MISO0p: J5.9, J7.9
/MISO0p_STIM: J4.1, J7.23
/MISO1m: J7.10, U1.8 (DOUT-)
/MISO1p: J7.11, U1.7 (DOUT+)
/MOSI0m_STIM: J4.7, J7.20
/MOSI0p_STIM: J4.8, J7.21
/MOSIm: J5.3, J7.6
/MOSIp: J5.4, J7.7
/PA10: J1.4, J10.1, J10.3
/PR7A: J1.12, J12.2, J13.1, R6.1
/PR7B: J1.14, J13.3, J14.1, R7.1
/PROGRAMN: J1.15, J3.4
/RSTN: J1.3, J2.12, J9.2
/SCLKm: J5.8, J7.4
/SCLKm_STIM: J4.4, J7.18
/SCLKp: J5.7, J7.5
/SCLKp_STIM: J4.3, J7.19
/SWCLK: J1.5, J2.6
/SWDIO: J1.7, J2.4
/TCK: J1.18, J3.8
/TDI: J1.13, J3.3
/TDO: J1.16, J3.2
/TMS: J1.11, J3.6
/VCC1: C9.1, C10.1, D1.1, J7.1, J7.24, J16.1
/VCC3P3V: C3.1, C4.1, C5.1, C6.1, C7.1, C8.1, J4.6, J4.12, J5.6, J5.12, J6.6, J6.12, J19.1, U1.1 (VCC)
/VCP_RX: J1.6, J15.4
/VCP_TX: J1.8, J15.2
/VSTIMm: C17.1, C18.1, J7.15, J16.5
/VSTIMp: C15.1, C16.1, J7.14, J16.3
unnamed: C1.1, J8.2A, J8.2B, J9.1
unnamed: C2.1, J11.2A, J11.2B, J12.1, R5.1
unnamed: D1.2, R1.2
unnamed: D2.2, R2.1
unnamed: D3.2, R3.1
unnamed: D4.1, J10.2
unnamed: D4.2, R4.1
unnamed: D5.1, J14.2
unnamed: D5.2, R8.1
unnamed: J2.14, J15.1
unnamed: J2.13, J15.3
unnamed: J6.1, U1.2 (DIN)

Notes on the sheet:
LGQ396 VF=1.9V @IF=2mA
